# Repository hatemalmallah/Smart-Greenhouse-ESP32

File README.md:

## Project Overview
This repository contains the hardware design, firmware, and IoT integration for an industrial-grade Smart Greenhouse control system. Unlike standard automated greenhouses, this project is engineered with a strong focus on **system reliability, fault tolerance, and precise actuator control**.

Powered by an **ESP32** microcontroller, the system monitors environmental parameters (Temperature, Humidity, Pressure, Gas, and Soil Moisture) via an I2C-managed **BME680** sensor. It intelligently controls 6 distinct actuators—represented by LEDs in this hardware prototype—simulating the following sub-systems: **Heating System, Cooling System, Water Pump, Grow Light, Ventilation Fan, and Humidifier**. The system manages all of these seamlessly using dual manual/automatic modes.

## Key Technical Highlights
* **Advanced Control Logic:** Implemented **Hysteresis algorithms** for stable, threshold-based actuator switching to prevent relay chattering and system instability.
* **Fault Tolerance & Safety:** Engineered a robust fail-safe mechanism. The system validates sensor data ranges, falls back to the last valid reading upon error, and executes an **Emergency Shutdown** after 5 consecutive invalid retries.
* **Signal Processing:** Utilized a Moving Average Filter (10-sample window) to clean noisy analog signals from sensors like soil moisture, preventing false triggering.
* **IoT & Remote Management:** Features bidirectional remote control via a custom **Telegram Bot API** and **Blynk** dashboard, alongside live data telemetry logged to **ThingSpeak** every 20 seconds for future Machine Learning (Predictive Maintenance) applications.
* **Custom Hardware:** Includes full PCB schematics and routing files designed specifically to handle the microcontroller, sensor bus, and actuator power management reliably.

## Hardware Components
* ESP32 Development Board (30-pin)
* BME680 Environmental Sensor
* LCD 16x2 with I2C module
* LDR Module (4-pin Photoresistor)
* 6x LED (5mm) - *Simulating Actuators*
* 6x Resistor (220 ohm)
* Buzzer (5V)
* MQ-2 Gas Sensor
* Push Button (4-pin)

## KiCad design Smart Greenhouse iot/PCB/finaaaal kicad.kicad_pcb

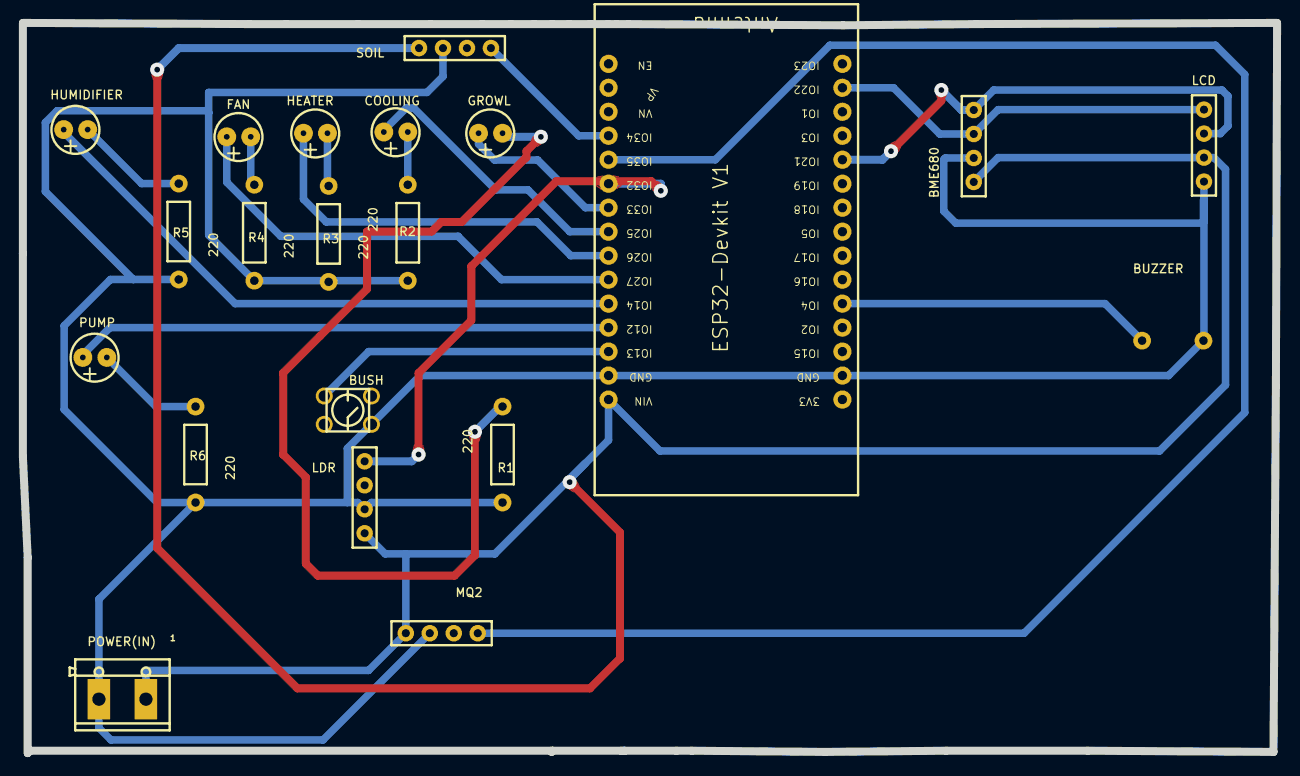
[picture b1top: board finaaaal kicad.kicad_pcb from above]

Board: 2 copper layers, 132.8 x 77.3 mm, 21 parts (0 on the bottom side), 21 nets.

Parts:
BME680: Female header1*4_I2C_LCD; FEMALEHEADER1*4_I2C_GDIP
BUSH: 4.5*4.5*5 DIP TACTILE BUTTON
BUZZER: BUZZER; BUZZER-12MM-NS-KIT
COOLING: LED_5MM COPY; LED-5MM-5MM
ESP32: ESP32-DEVKIT-V1-30PIN NORMALIZED COPY; ESP32-DEVKITV1_ESP32-DEVKITV1
FAN: LED_5MM COPY; LED-5MM-5MM
GROWL: LED_5MM COPY; LED-5MM-5MM
HEATER: LED_5MM COPY; LED-5MM-5MM
HUMIDIFIER: LED_5MM COPY; LED-5MM-5MM
LCD: Female header1*4_I2C_LCD; FEMALEHEADER1*4_I2C_GDIP
LDR: Female header1*4_I2C_LCD; FEMALEHEADER1*4_I2C_GDIP
MQ2: Female header1*4_I2C_LCD; FEMALEHEADER1*4_I2C_GDIP
POWER(IN): CON_TERMINAL_BLOCK_02-5MM; TERMINAL_BLOCK_2P_5
PUMP: LED_5MM COPY; LED-5MM-5MM
R1, R2, R3, R4, R5, R6: 220; AXIAL-0.4
SOIL: Female header1*4_I2C_LCD; FEMALEHEADER1*4_I2C_GDIP

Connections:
1_D4: BUZZER.+, ESP32.D4
1_D12: ESP32.D12, PUMP.1
1_D13: BUSH.4, ESP32.D13
1_D14: ESP32.D14, HUMIDIFIER.1
1_D21: BME680.1, ESP32.D21, LCD.3
1_D22: BME680.2, ESP32.D22, LCD.4
1_D25: COOLING.1, ESP32.D25
1_D26: ESP32.D26, HEATER.1
1_D27: ESP32.D27, FAN.1
1_D32: ESP32.D32, LDR.1
1_D33: ESP32.D33, GROWL.1
1_D34: ESP32.D34, SOIL.1
1_D35: ESP32.D35, MQ2.1
+5V: BME680.4, ESP32.VIN, LCD.2, LDR.4, MQ2.4, POWER(IN).1, SOIL.4
GND: BME680.3, BUSH.1, BUZZER.-, ESP32.GND, ESP32.GND2, LCD.1, LDR.3, MQ2.3, POWER(IN).2, R1.1, R2.1, R3.2, R4.2, R5.2, R6.2, SOIL.3
R1_2: GROWL.2, R1.2
R2_2: COOLING.2, R2.2
R3_1: HEATER.2, R3.1
R4_1: FAN.2, R4.1
R5_1: HUMIDIFIER.2, R5.1
R6_1: PUMP.2, R6.1

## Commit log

2026-05-20 README.md
